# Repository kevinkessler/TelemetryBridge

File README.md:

TelemetryBridge
===============

Bridge to send APM USART Telemetry to a Spektrum Telemetry Module

See http://kesslerarduino.wordpress.com/2014/02/05/telemetry-bridge/ for a complete disscussion

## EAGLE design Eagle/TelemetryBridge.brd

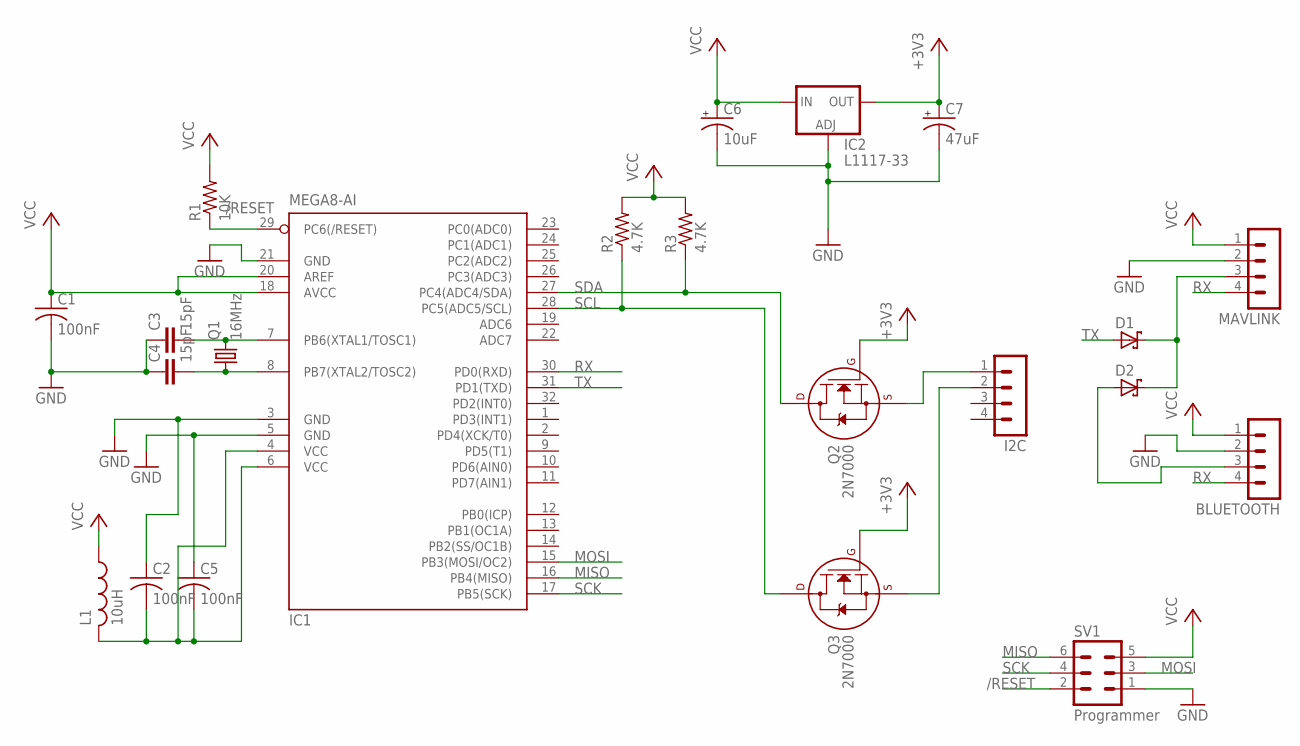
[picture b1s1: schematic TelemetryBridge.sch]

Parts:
BLUETOOTH: MA04-1
C1, C2, C5: 100nF; C0805
C3, C4: 15pF; C0805
C6: 10uF; PANASONIC_C
C7: 47uF; PANASONIC_D
D1, D2: SCHOTTKY-DIODE; DO-214AC
I2C: MA04-1
IC1: MEGA8-AI; TQFP32-08; MPN ATMEGA8-16AU
IC2: L1117-33; DPACK
L1: 10uH; 0805
MAVLINK: MA04-1
Q1: 16MHz; CSM-7X-DU
Q2, Q3: 2N7000; SOT-23
R1: 10K; R0805
R2, R3: 4.7K; R0805
SV1: Programmer; KEVINSLIB_MA03-2

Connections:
+3V3: C7.+, IC2.4 (OUT), Q2.1 (G), Q3.1 (G)
/RESET: IC1.29 (PC6(/RESET)), R1.1, SV1.2
GND: BLUETOOTH.2, C1.2, C2.1, C3.1, C4.1, C5.1, C6.-, C7.-, IC1.3 (GND), IC1.5 (GND), IC1.21 (GND), IC2.1 (ADJ), MAVLINK.2, SV1.1
MISO: IC1.16 (PB4(MISO)), SV1.6
MOSI: IC1.15 (PB3(MOSI/OC2)), SV1.3
unnamed: BLUETOOTH.3, D2.A
unnamed: D1.C, D2.C, MAVLINK.3
unnamed: C4.2, IC1.8 (PB7(XTAL2/TOSC2)), Q1.1
unnamed: C2.2, C5.2, IC1.4 (VCC), IC1.6 (VCC), L1.2
unnamed: I2C.1, Q2.2 (S)
unnamed: C3.2, IC1.7 (PB6(XTAL1/TOSC1)), Q1.2
unnamed: I2C.2, Q3.2 (S)
RX: BLUETOOTH.4, IC1.30 (PD0(RXD)), MAVLINK.4
SCK: IC1.17 (PB5(SCK)), SV1.4
SCL: IC1.28 (PC5(ADC5/SCL)), Q3.3 (D), R2.1
SDA: IC1.27 (PC4(ADC4/SDA)), Q2.3 (D), R3.1
TX: D1.A, IC1.31 (PD1(TXD))
VCC: BLUETOOTH.1, C1.1, C6.+, IC1.18 (AVCC), IC1.20 (AREF), IC2.3 (IN), L1.1, MAVLINK.1, R1.2, R2.2, R3.2, SV1.5

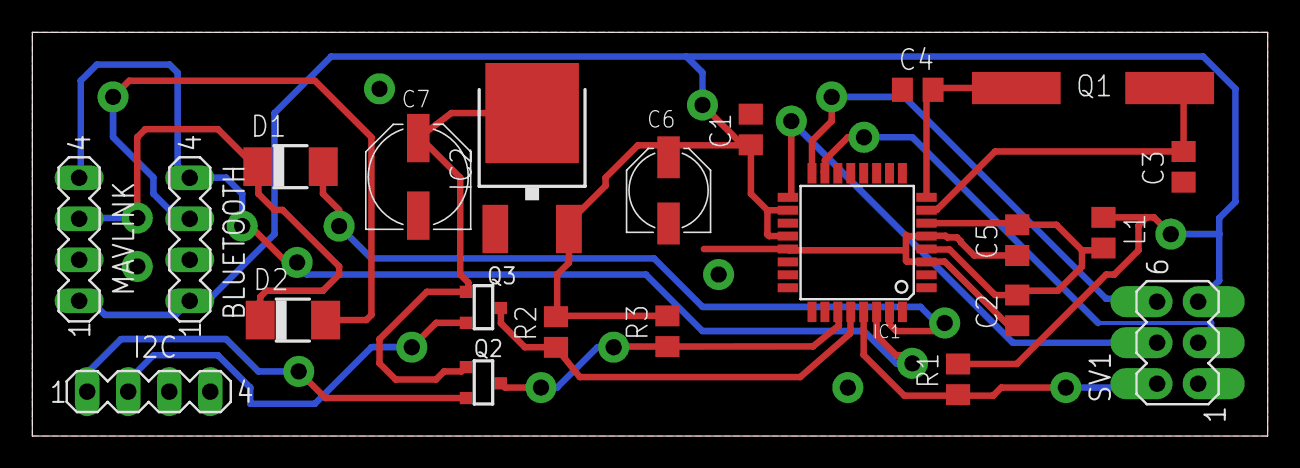
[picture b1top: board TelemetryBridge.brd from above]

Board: 2 copper layers, 76.5 x 25.0 mm, 22 parts (0 on the bottom side), 18 nets.

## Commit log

2014-02-05 Initial Upload
2014-02-05 Circuit Board
